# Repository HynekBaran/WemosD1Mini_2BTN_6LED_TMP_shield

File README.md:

# WemosD1Mini_2BTN_6LED_TMP_shield
Wemos D1 Mini shield (2 buttons, 6 LEDs, TMP sensor) PCB

Wemos D1 shield for 
- 2 buttons/switches,
- 6 LEDs (incl. resistors), 
- temperature sensor (incl. pullup resistor) and 
- photoresistor (pullup res. incl.).

Pinheads for all data lines available.

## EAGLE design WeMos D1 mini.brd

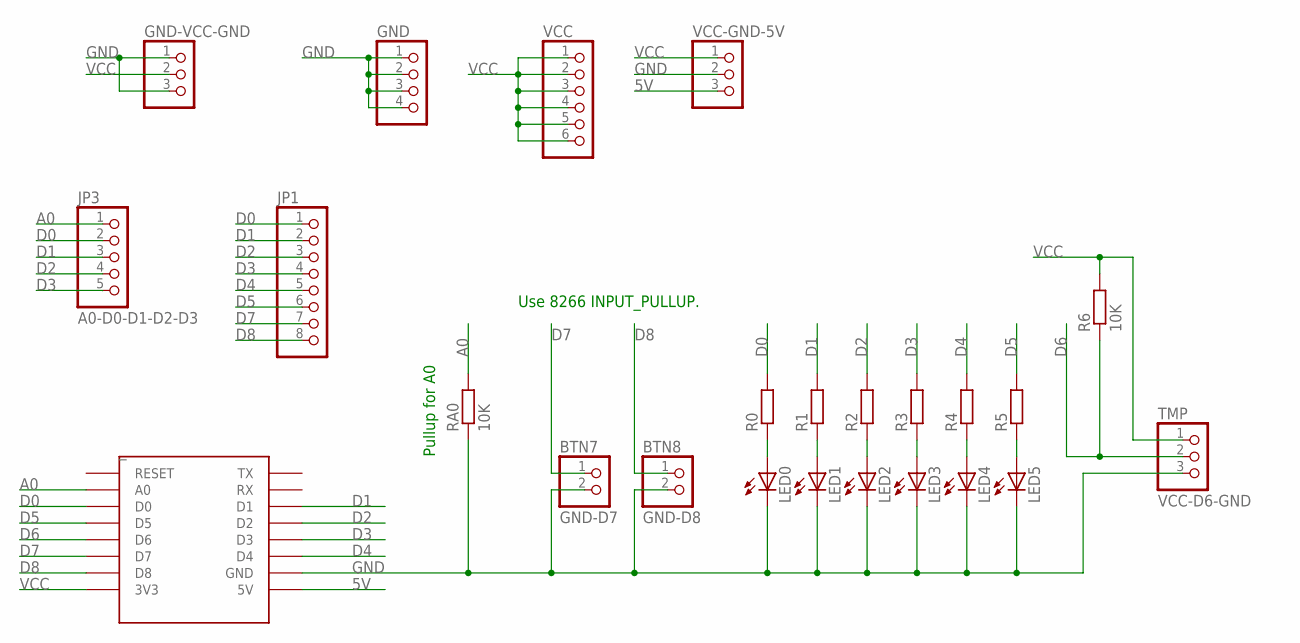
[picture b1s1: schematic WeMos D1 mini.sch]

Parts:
BTN7: GND-D7; 1X02/OCT
BTN8: GND-D8; 1X02/OCT
GND: PINHD-1X4/OCT; 1X04/OCT
GND-VCC-GND: PINHD-1X3/OCT; 1X03/OCT
JP1: PINHD-1X8/OCT; 1X08/OCT
JP3: A0-D0-D1-D2-D3; 1X05/OCT
LED0, LED1, LED2, LED3, LED4, LED5: LED3MM
R0, R1, R2, R3, R4, R5: R-EU_0204/5; 0204/5
R6: 10K; 0204/5
RA0: 10K; 0204/5
TMP: VCC-D6-GND; 1X03/OCT
VCC: PINHD-1X6/OCT; 1X06/OCT
VCC-GND-5V: PINHD-1X3/OCT; 1X03/OCT
_: WEMOS-D1-MINI

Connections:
5V: VCC-GND-5V.3, _.5V
A0: JP3.1, RA0.2, _.A0
D0: JP1.1, JP3.2, R0.2, _.D0
D1: JP1.2, JP3.3, R1.2, _.D1
D2: JP1.3, JP3.4, R2.2, _.D2
D3: JP1.4, JP3.5, R3.2, _.D3
D4: JP1.5, R4.2, _.D4
D5: JP1.6, R5.2, _.D5
D6: R6.1, TMP.2, _.D6
D7: BTN7.1, JP1.7, _.D7
D8: BTN8.1, JP1.8, _.D8
GND: BTN7.2, BTN8.2, GND.1, GND.2, GND.3, GND.4, GND-VCC-GND.1, GND-VCC-GND.3, LED0.K (C), LED1.K (C), LED2.K (C), LED3.K (C), LED4.K (C), LED5.K (C), RA0.1, TMP.3, VCC-GND-5V.2, _.GND
unnamed: LED5.A, R5.1
unnamed: LED4.A, R4.1
unnamed: LED3.A, R3.1
unnamed: LED2.A, R2.1
unnamed: LED1.A, R1.1
unnamed: LED0.A, R0.1
VCC: GND-VCC-GND.2, R6.2, TMP.1, VCC.1, VCC.2, VCC.3, VCC.4, VCC.5, VCC.6, VCC-GND-5V.1, _.3V3

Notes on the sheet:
Pullup for A0
Use 8266 INPUT_PULLUP.

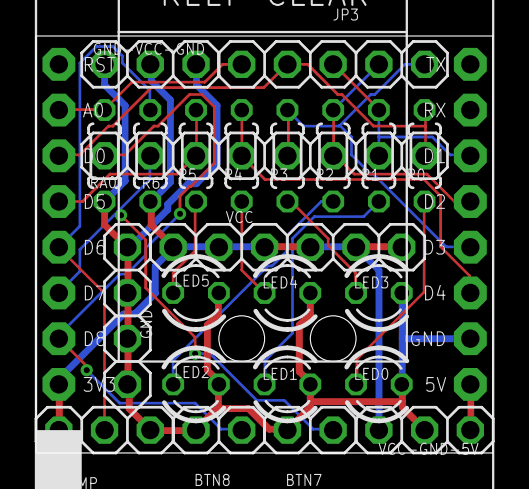
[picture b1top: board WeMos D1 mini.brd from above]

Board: 2 copper layers, 25.4 x 23.2 mm, 24 parts (0 on the bottom side), 19 nets.

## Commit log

2017-09-13 .gitignore
2017-09-13 Changed esp8266modules.lbr (esthetics)
2017-09-13 esp8266modules.lbr pins changed to octagon shape
2017-09-13 1st prototype candidate 1
2017-09-17 gerbers
2017-09-17 OMRON SWITCH onboard buttons
2017-09-17 https://PCBs.io/share/z5oeo
2017-09-17 Omitted drill greber
